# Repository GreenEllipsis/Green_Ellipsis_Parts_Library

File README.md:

==Main folder==
- Parts go in this folder
- Each part or assembly is in its own folder (or a zipped file of the folder)
- Folder name is partnumber_description or just partnumber
- partnumber format is YYDDDabcNN where abc are your initials and NN is a unique alphanumeric for that YYDDDabc combination

==Part folder==
- contains the part file
- part file name is partnumber_REV x_description, where x is the REV number, REV x and description are optional
- REV follows the ASME Y.100 Appendix C(?) sequence of -, A, B, C, etc
- optionally contains a meta data file
- may contain files used to create the part file or files the part was derived from

==Meta Data File==
- meta data files is in YAML format
- is named partnumber.yaml, where partnumber is the partnumber
- has these optional key/value pairs
  - author:
  - copyright:
  - license:
  - derived from: filename or URL
  - file format: 
  - last edited using: software name, version
  - last updated:
  - next higher assembly:
  - system:

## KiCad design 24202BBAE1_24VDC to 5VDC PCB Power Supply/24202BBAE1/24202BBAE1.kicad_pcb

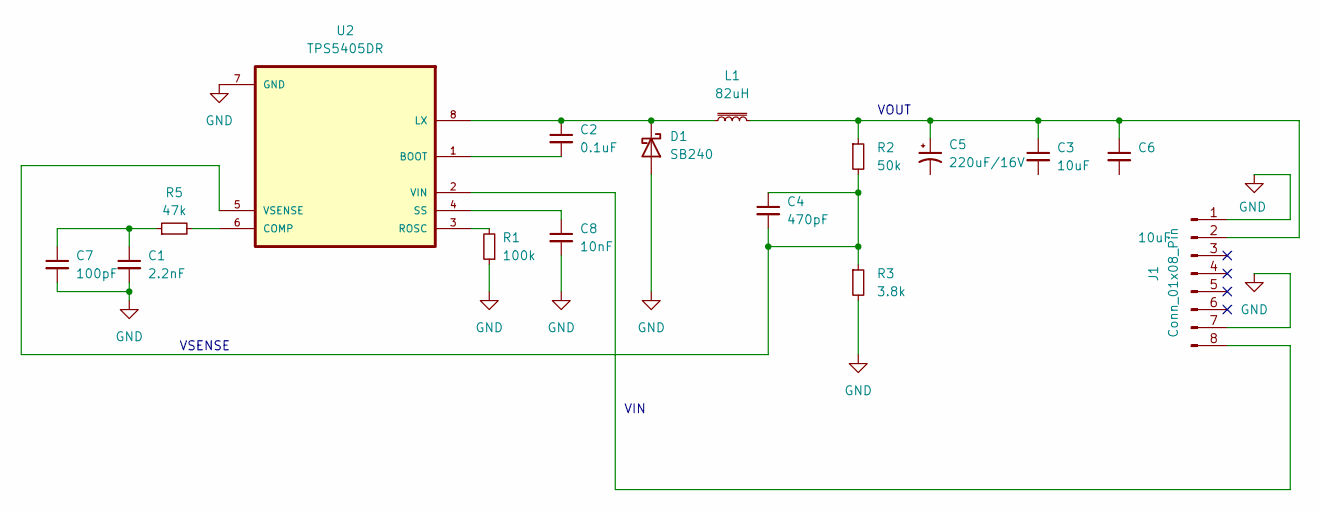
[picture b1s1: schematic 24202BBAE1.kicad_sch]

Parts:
C1: 2.2nF; C_0402_1005Metric
C2: 0.1uF; C_0402_1005Metric
C3, C6: 10uF; C_0402_1005Metric
C4: 470pF; C_0402_1005Metric
C5: 220uF/16V; CP_Elec_5x3
C7: 100pF; C_0402_1005Metric
C8: 10nF; C_0402_1005Metric
D1: SB240; D_0402_1005Metric
J1: Conn_01x08_Pin; PinHeader_1x07_P2.54mm_Vertical_SMD_Pin1Left
L1: 82uH; IND_BOURNS_SDR0302
R1: 100k; R_0402_1005Metric
R2: 50k; R_0402_1005Metric
R3: 3.8k; R_0402_1005Metric
R5: 47k; R_0402_1005Metric
U2: TPS5405DR; SOIC127P599X175-8N

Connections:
GND: C1.2, C7.2, C8.2, D1.2 (A), J1.1, J1.7, R1.1, R3.2, U2.7 (GND)
unnamed: C1.1, C7.1, R5.1
unnamed: C2.1, D1.1 (K), L1.1, U2.8 (LX)
unnamed: C3.1, C5.1, C6.1, J1.2, L1.2, R2.1
unnamed: C2.2, U2.1 (BOOT)
unnamed: R5.2, U2.6 (COMP)
unnamed: J1.8, U2.2 (VIN)
unnamed: R1.2, U2.3 (ROSC)
unnamed: C8.1, U2.4 (SS)
unnamed: C4.1, C4.2, R2.2, R3.1, U2.5 (VSENSE)

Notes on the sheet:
VSENSE
VOUT
VIN

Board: 2 copper layers, 15 parts (0 on the bottom side), 5 nets, no tracks yet.

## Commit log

2023-12-23 checkpoint
2023-12-23 checkpoint
    added spool end cap
2023-12-24 checkpoint
    * fix handedness of spool core
    * add spool rod spacer
2023-12-25 checkpoint
    * spool rod spacer add automatic preview rendering
    * add 23356BBA01 Volcano Heater Block
    * add 23356BBA02 Heather Block Mount (WIP)
2023-12-26 checkpoint
    adding mounting_plate WIP
    heater_block_mount WIP
2024-01-31 added autotruder logo and other autotruder parts
2024-02-04 heater block mounting plate
    refactor Autotruder into a BOSL2 module.
    Fix mounting_plate.scad to place anchors correctly in Z
2024-06-25 chechpoint
2024-12-17 added Fort Alano and much more
2024-12-17 reorganize under BBA02
2024-12-22 PVC Fort Alano updates
    bigger through hole is the only significant change. Some STLs generated. Not all with the newer size hole
